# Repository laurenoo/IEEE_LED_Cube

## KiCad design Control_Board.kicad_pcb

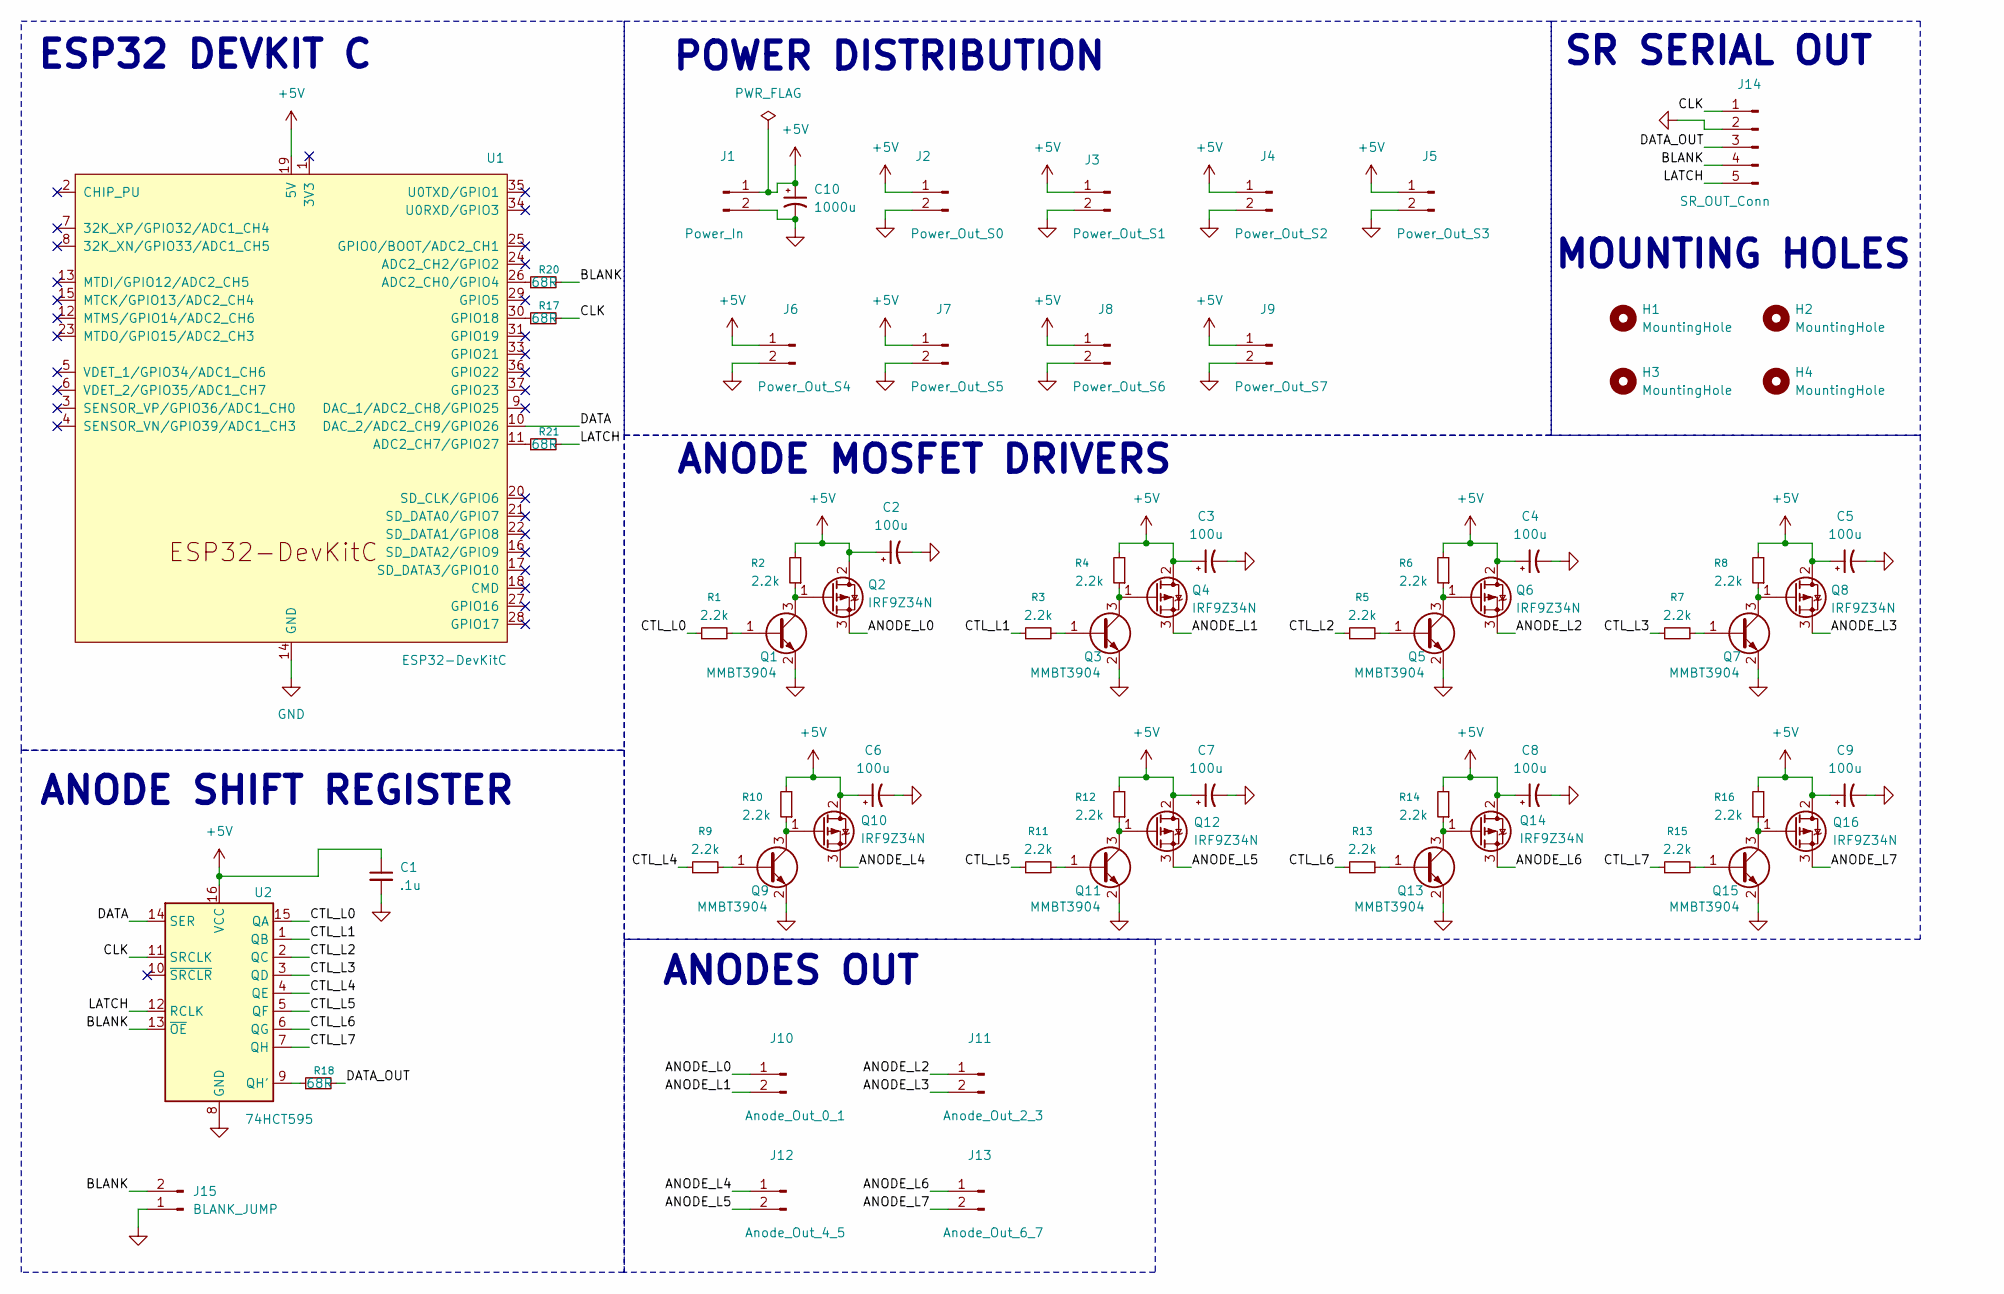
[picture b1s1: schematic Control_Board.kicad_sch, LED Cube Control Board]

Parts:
C1: .1u
C2, C3, C4, C5, C6, C7, C8, C9: 100u; CP_Elec_6.3x7.7; Mfr # 865080545012
C10: 1000u; C_Radial_D10.0mm_H20.0mm_P5.00mm; Mfr # 865080545012
H1, H2, H3, H4: MountingHole; MountingHole_3.2mm_M3
J1: Power_In; JST_VH_B2P-VH_1x02_P3.96mm_Vertical; Mfr # B2P-VH
J2: Power_Out_S0; JST_XH_B2B-XH-A_1x02_P2.50mm_Vertical; Mfr # B2B-XH-A
J3: Power_Out_S1; JST_XH_B2B-XH-A_1x02_P2.50mm_Vertical; Mfr # B2B-XH-A
J4: Power_Out_S2; JST_XH_B2B-XH-A_1x02_P2.50mm_Vertical; Mfr # B2B-XH-A
J5: Power_Out_S3; JST_XH_B2B-XH-A_1x02_P2.50mm_Vertical; Mfr # B2B-XH-A
J6: Power_Out_S4; JST_XH_B2B-XH-A_1x02_P2.50mm_Vertical; Mfr # B2B-XH-A
J7: Power_Out_S5; JST_XH_B2B-XH-A_1x02_P2.50mm_Vertical; Mfr # B2B-XH-A
J8: Power_Out_S6; JST_XH_B2B-XH-A_1x02_P2.50mm_Vertical; Mfr # B2B-XH-A
J9: Power_Out_S7; JST_XH_B2B-XH-A_1x02_P2.50mm_Vertical; Mfr # B2B-XH-A
J10: Anode_Out_0_1; JST_VH_B2P-VH_1x02_P3.96mm_Vertical; Mfr # B2B-XH-A
J11: Anode_Out_2_3; JST_VH_B2P-VH_1x02_P3.96mm_Vertical; Mfr # B2B-XH-A
J12: Anode_Out_4_5; JST_VH_B2P-VH_1x02_P3.96mm_Vertical; Mfr # B2B-XH-A
J13: Anode_Out_6_7; JST_VH_B2P-VH_1x02_P3.96mm_Vertical; Mfr # B2B-XH-A
J14: SR_OUT_Conn; JST_PH_B5B-PH-K_1x05_P2.00mm_Vertical; Mfr # B5B-PH-K-S(LF)(SN)
J15: BLANK_JUMP; PinHeader_1x02_P2.54mm_Vertical
Q1, Q3, Q5, Q7, Q9, Q11, Q13, Q15: MMBT3904; SOT-23; Mfr # MMBT3904-G
Q2, Q4, Q6, Q8, Q10, Q12, Q14, Q16: IRF9Z34N; TO-220-3_Vertical; Mfr # IRF9Z34NPBF
R1, R2, R3, R4, R5, R6, R7, R8, R9, R10, R11, R12, R13, R14, R15, R16: 2.2k; R_0805_2012Metric_Pad1.20x1.40mm_HandSolder; Mfr # 0805W8J0222T5E
R17, R18, R20, R21: 68R; R_0805_2012Metric_Pad1.20x1.40mm_HandSolder; Mfr # 0805W8J0222T5E
U1: ESP32-DevKitC
U2: 74HCT595; SOIC-16_3.9x9.9mm_P1.27mm; Mfr # SN74HC595DR

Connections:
+5V: C1.1, C2.1, C3.1, C4.1, C5.1, C6.1, C7.1, C8.1, C9.1, C10.1, J1.1, J2.1, J3.1, J4.1, J5.1, J6.1, J7.1, J8.1, J9.1, Q2.2 (D), Q4.2 (D), Q6.2 (D), Q8.2 (D), Q10.2 (D), Q12.2 (D), Q14.2 (D), Q16.2 (D), R2.2, R4.2, R6.2, R8.2, R10.2, R12.2, R14.2, R16.2, U1.19 (5V), U2.16 (VCC)
/ANODE_L0: J10.1, Q2.3 (S)
/ANODE_L1: J10.2, Q4.3 (S)
/ANODE_L2: J11.1, Q6.3 (S)
/ANODE_L3: J11.2, Q8.3 (S)
/ANODE_L4: J12.1, Q10.3 (S)
/ANODE_L5: J12.2, Q12.3 (S)
/ANODE_L6: J13.1, Q14.3 (S)
/ANODE_L7: J13.2, Q16.3 (S)
/BLANK: J14.4, J15.2, R20.2, U2.13 (~OE)
/CLK: J14.1, R17.2, U2.11 (SRCLK)
/CTL_L0: R1.1, U2.15 (QA)
/CTL_L1: R3.1, U2.1 (QB)
/CTL_L2: R5.1, U2.2 (QC)
/CTL_L3: R7.1, U2.3 (QD)
/CTL_L4: R9.1, U2.4 (QE)
/CTL_L5: R11.1, U2.5 (QF)
/CTL_L6: R13.1, U2.6 (QG)
/CTL_L7: R15.1, U2.7 (QH)
/DATA: U1.10 (DAC_2/ADC2_CH9/GPIO26), U2.14 (SER)
/DATA_OUT: J14.3, R18.2
/LATCH: J14.5, R21.2, U2.12 (RCLK)
GND: C1.2, C2.2, C3.2, C4.2, C5.2, C6.2, C7.2, C8.2, C9.2, C10.2, J1.2, J2.2, J3.2, J4.2, J5.2, J6.2, J7.2, J8.2, J9.2, J14.2, J15.1, Q1.2 (E), Q3.2 (E), Q5.2 (E), Q7.2 (E), Q9.2 (E), Q11.2 (E), Q13.2 (E), Q15.2 (E), U1.14 (GND), U1.32 (GND), U1.38 (GND), U2.8 (GND)
unnamed: Q1.1 (B), R1.2
unnamed: Q1.3 (C), Q2.1 (G), R2.1
unnamed: Q3.1 (B), R3.2
unnamed: Q3.3 (C), Q4.1 (G), R4.1
unnamed: Q5.1 (B), R5.2
unnamed: Q5.3 (C), Q6.1 (G), R6.1
unnamed: Q7.1 (B), R7.2
unnamed: Q7.3 (C), Q8.1 (G), R8.1
unnamed: Q9.1 (B), R9.2
unnamed: Q9.3 (C), Q10.1 (G), R10.1
unnamed: Q11.1 (B), R11.2
unnamed: Q11.3 (C), Q12.1 (G), R12.1
unnamed: Q13.1 (B), R13.2
unnamed: Q13.3 (C), Q14.1 (G), R14.1
unnamed: Q15.1 (B), R15.2
unnamed: Q15.3 (C), Q16.1 (G), R16.1
unnamed: R20.1, U1.26 (ADC2_CH0/GPIO4)
unnamed: R21.1, U1.11 (ADC2_CH7/GPIO27)
unnamed: R17.1, U1.30 (GPIO18)
unnamed: R18.1, U2.9 (QH')

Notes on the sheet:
ANODES OUT
ANODE MOSFET DRIVERS
SR SERIAL OUT
ANODE SHIFT REGISTER
MOUNTING HOLES
ESP32 DEVKIT C
POWER DISTRIBUTION

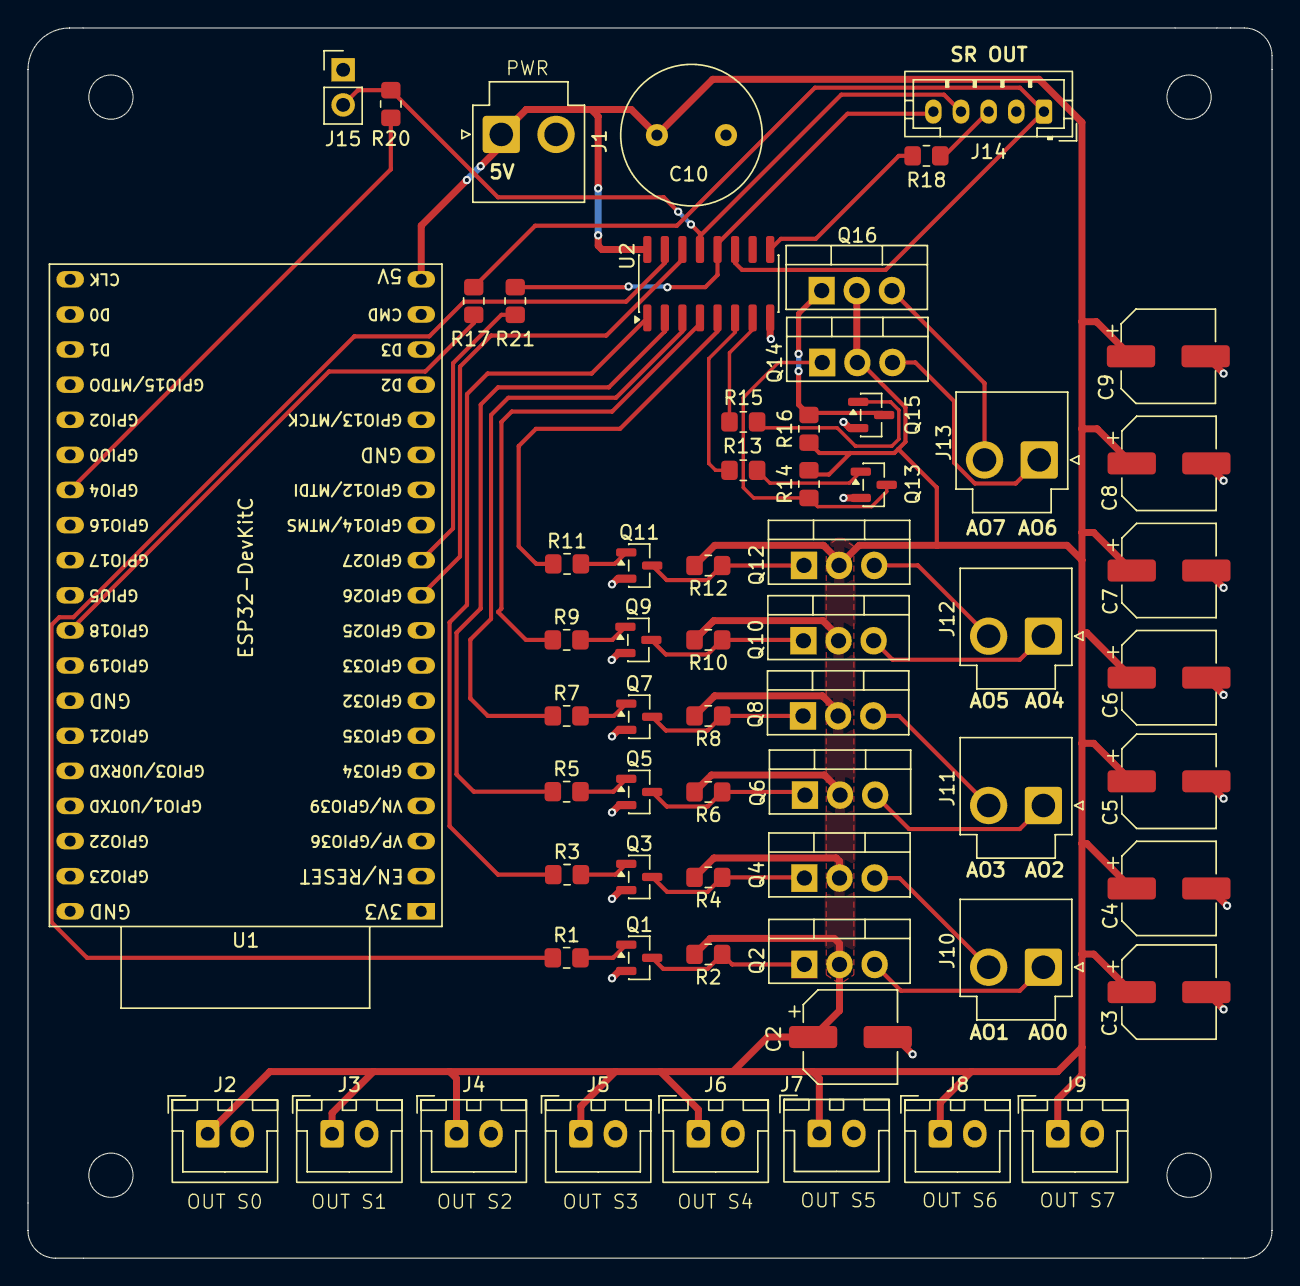
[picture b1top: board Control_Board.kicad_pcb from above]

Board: 2 copper layers, 90.0 x 89.0 mm, 66 parts (0 on the bottom side), 43 nets.
